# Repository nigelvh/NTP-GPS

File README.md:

# NTP-GPS
Custom GPS Hardware for use with NTP Stratum 1 servers, along with system configuration documentation.

## Hardware
The hardware designs for my specific device. There are many GPS options for building a Stratum 1 NTP server. This is just one take on it.

## Firmware
The firmware code and binaries for the device described in the Hardware section. Built in the Arduino IDE to be maximally approachable.

## Software
Configuration guides for setting up NTPd, NTPsec, or Chrony on Ubuntu, Debian, Alma, or Rocky to acquire the PPS signals provided by the GPS and use them to discipline the local clock and act as a Stratum 1 server.

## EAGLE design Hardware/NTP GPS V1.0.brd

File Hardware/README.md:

# NTP GPS Hardware
This is a custom piece of hardware for use with stratum 1 NTP servers to provide a simple and flexible way of getting timing data into the NTP daemon of choice.

This is not a wholly unique device, there are other devices that perform similar functions or some subset thereof. It is certainly not the only way to accomplish the task. It was designed as a means to address the most common shortfalls I have seen and for the enjoyment of making it.

This device uses a good quality GPS receiver with precise Pulse Per Second (PPS) output, and exposes both the NMEA data, as well as the PPS signal on the DCD serial line over both USB (less precise timing) as well as RS232 (more precise timing) simultaneously. This is done to provide maximum flexibility to the user's use case. If a hardware serial port is available, use that as it will provide more precise timing. If only USB is available, that is also functional.

Many inexpensive off the shelf GPS receivers do not expose the PPS signals properly on the DCD serial line making precise timing difficult to capture, or expensive time servers are available which are double to many times the cost of this device. This device was designed to fit the middle ground of a quality time source for a use case where an existing server is available, and can be configured per the instructions in the Software folder of this repository.

The schematic and board files have been created in Eagle, though I cannot guarantee how they will load without all the the associated libraries. There are additionally exported images of the schematic and board designs available for reference without using the Eagle software package.

A parts text file has been included to cover some of the more important, or more specific parts for the design. It is not all inclusive (I didn't include the passives for example), but it covers the main components, as well as some useful accessories (cables, antenna, etc).

## Design Choices
### ESP32
The ESP32 was chosen as the microcontroller for this project as it is able to handle three simultaneous hardware UARTs, is reasonably inexpensive, and is easily programmed with the Arduino IDE. In some measures it is overkill for this application, but being inexpensive and easily programmable make it more approachable to more people.

### uBlox MAX-M8 GPS
The uBlox MAX-M8 GPS device was chosen for being a quality GPS chipset, that I am familiar with, and has good timing parameters. The MAX series is not the specifically timing oriented line, however it is more than accurate enough for NTP requirements. It is able to track multiple constellations and has good RF sensitivity. I have fitted it with the associated power circuitry to supply an active GPS antenna which is essential for longer runs of cable, which is likely to be required to span between a rooftop antenna placement and a server located inside a building/datacenter.

### FTDI UART and ST232 Serial Driver
There are microcontroller choices available that could do USB natively, as well as there are other RS232 driver chipsets that may be cheaper. These were chosen for being commonly available, widely used and proven, as well as having the required inputs/outputs to handle the PPS signal over the DCD line, which not all devices support.

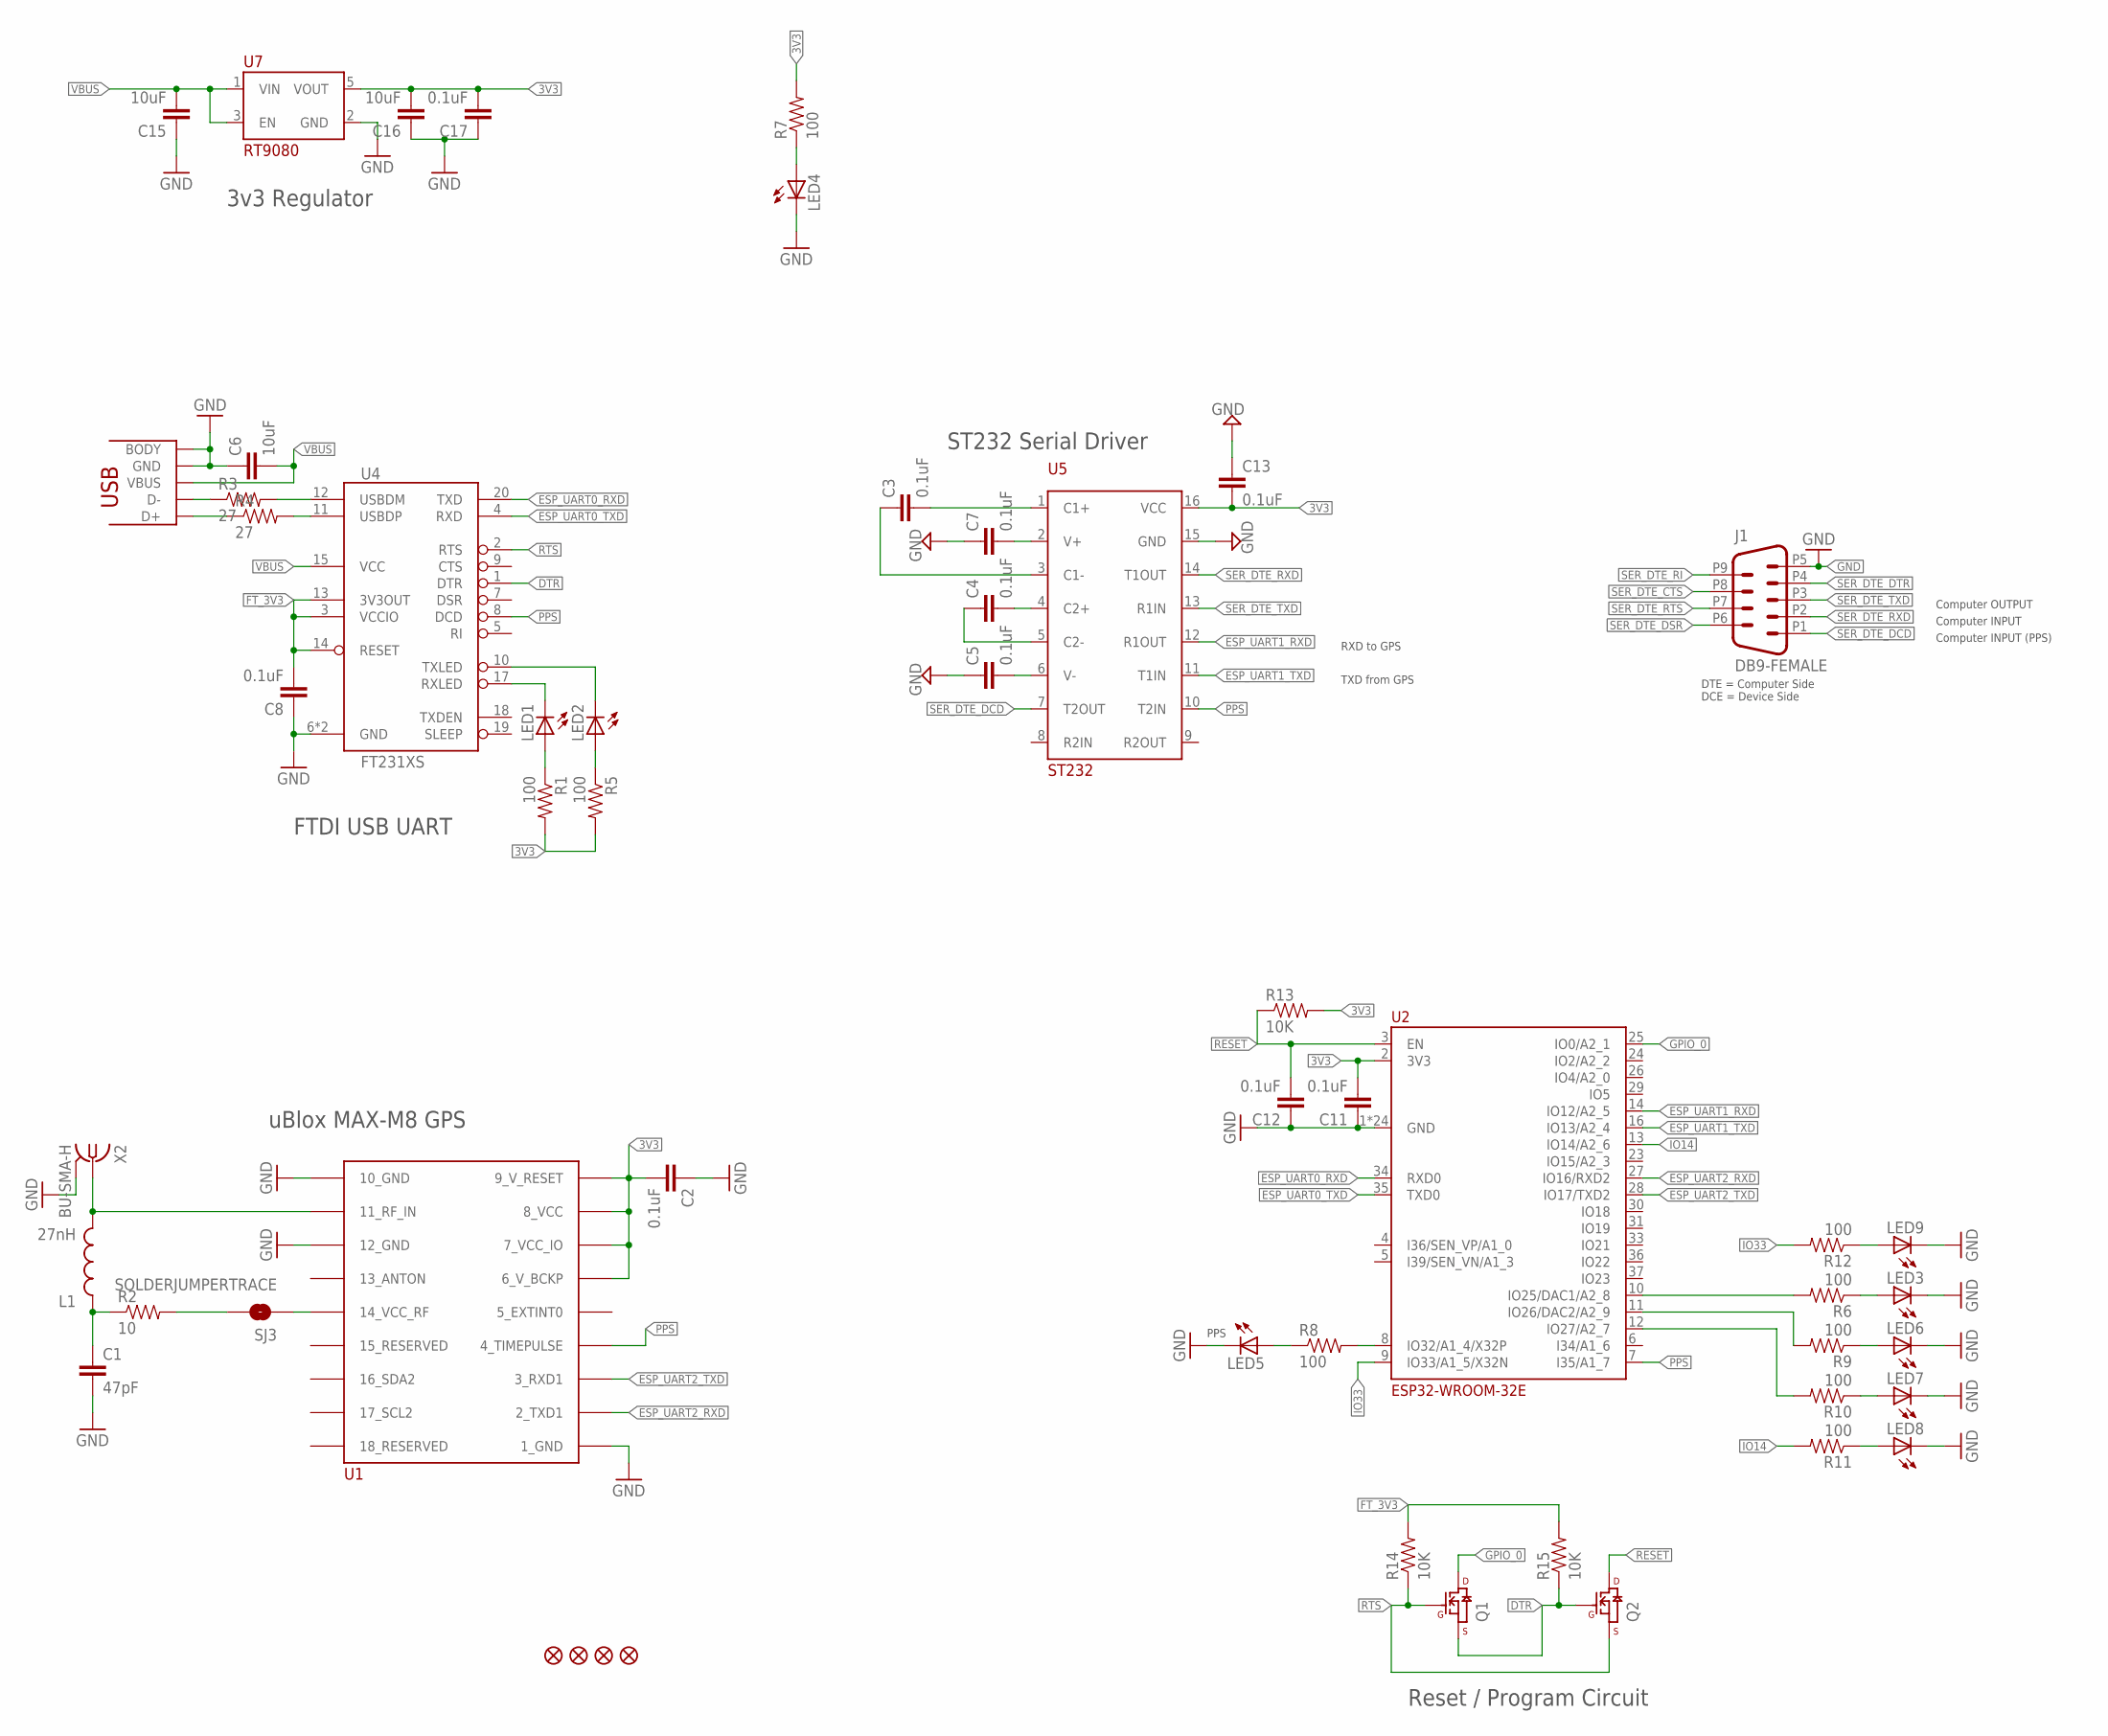
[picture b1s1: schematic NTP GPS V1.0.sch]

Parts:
C1: 47pF; 0603-CAP
C2, C3, C4, C5, C7, C8, C11, C12, C13, C17: 0.1uF; 0603-CAP
C6, C15, C16: 10uF; 1206
FID1, FID2, FID3, FID4: FIDUCIAL
J1: DB9-FEMALE; AMP_DELTAD_D09S13B4GV00LF
L1: 27nH; 0603
LED1, LED2, LED3, LED4, LED5, LED6, LED7, LED8, LED9: LED; LED_QBL7XX80D-MP4A
Q1, Q2: MOSFET_N_CHANNELSI1308; SC-70-3
R1, R5, R6, R7, R8, R9, R10, R11, R12: 100; 0603-RES
R2: 10; 0603-RES
R3, R4: 27; 0603-RES
R13, R14, R15: 10K; 0603-RES
SJ3: SOLDERJUMPERTRACE; SJ_2S-TRACE
U1: UBLOX_MAX
U2: ESP32-WROOM-32E
U4: FT231XS; SSOP-20
U5: ST232; SSOP-16
U7: RT9080; SOT-23-5
U$1: USB-MICROB; USB-MICROB-10118192
X2: BU-SMA-H

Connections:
3V3: C2.2, C11.2, C13.2, C16.2, C17.2, R1.2, R5.2, R7.2, R13.2, U1.6_V_BCKP, U1.7_VCC_IO, U1.8_VCC, U1.9_V_RESET, U2.2 (3V3), U5.16 (VCC), U7.5 (VOUT)
DTR: Q1.P$2 (S), Q2.P$1 (G), R15.1, U4.1 (DTR)
ESP_UART0_RXD: U2.34 (RXD0), U4.20 (TXD)
ESP_UART0_TXD: U2.35 (TXD0), U4.4 (RXD)
ESP_UART1_RXD: U2.14 (IO12/A2_5), U5.12 (R1OUT)
ESP_UART1_TXD: U2.16 (IO13/A2_4), U5.11 (T1IN)
ESP_UART2_RXD: U1.2_TXD1, U2.27 (IO16/RXD2)
ESP_UART2_TXD: U1.3_RXD1, U2.28 (IO17/TXD2)
FT_3V3: C8.2, R14.2, R15.2, U4.3 (VCCIO), U4.13 (3V3OUT), U4.14 (RESET)
GND: C1.2, C2.1, C5.1, C6.1, C7.1, C8.1, C11.1, C12.1, C13.1, C15.1, C16.1, C17.1, J1.P5 (5), LED3.C, LED4.C, LED5.C, LED6.C, LED7.C, LED8.C, LED9.C, U1.1_GND, U1.10_GND, U1.12_GND, U2.1 (GND), U2.15 (GND), U2.38 (GND), U2.P$1 (GND), U2.P$2 (GND), U2.P$3 (GND), U2.P$4 (GND), U2.P$5 (GND), U2.P$6 (GND), U2.P$7 (GND), U2.P$8 (GND), U2.P$9 (GND), U2.P$10 (GND), U2.P$11 (GND), U2.P$12 (GND), U2.PAD@1 (GND), U2.PAD@2 (GND), U2.PAD@3 (GND), U2.PAD@4 (GND), U2.PAD@5 (GND), U2.PAD@6 (GND), U2.PAD@7 (GND), U2.PAD@8 (GND), U2.PAD@9 (GND), U4.6 (GND), U4.16 (GND), U5.15 (GND), U7.2 (GND), U$1.5 (GND), U$1.BODY@1 (BODY), U$1.BODY@2 (BODY), U$1.BODY@3 (BODY), U$1.BODY@4 (BODY), U$1.BODY@5 (BODY), U$1.BODY@6 (BODY), X2.2, X2.3 (2), X2.4 (2), X2.5 (2)
GPIO_0: Q1.P$3 (D), U2.25 (IO0/A2_1)
IO14: R11.2, U2.13 (IO14/A2_6)
IO33: R12.2, U2.9 (IO33/A1_5/X32N)
unnamed: L1.2, U1.11_RF_IN, X2.1
unnamed: R8.2, U2.8 (IO32/A1_4/X32P)
unnamed: SJ3.1, U1.14_VCC_RF
unnamed: C1.1, L1.1, R2.1
unnamed: C7.2, U5.2 (V+)
unnamed: C5.2, U5.6 (V-)
unnamed: R3.1, U$1.2 (D-)
unnamed: R4.1, U$1.3 (D+)
unnamed: LED2.A, R5.1
unnamed: C3.2, U5.1 (C1+)
unnamed: LED3.A, R6.1
unnamed: C4.2, U5.4 (C2+)
unnamed: LED1.C, U4.17 (RXLED)
unnamed: C3.1, U5.3 (C1-)
unnamed: C4.1, U5.5 (C2-)
unnamed: LED2.C, U4.10 (TXLED)
unnamed: R4.2, U4.11 (USBDP)
unnamed: R3.2, U4.12 (USBDM)
unnamed: R2.2, SJ3.2
unnamed: LED4.A, R7.1
unnamed: LED5.A, R8.1
unnamed: LED1.A, R1.1
unnamed: LED6.A, R9.1
unnamed: LED7.A, R10.1
unnamed: LED8.A, R11.1
unnamed: LED9.A, R12.1
unnamed: R6.2, U2.10 (IO25/DAC1/A2_8)
unnamed: R9.2, U2.11 (IO26/DAC2/A2_9)
unnamed: R10.2, U2.12 (IO27/A2_7)
PPS: U1.4_TIMEPULSE, U2.7 (I35/A1_7), U4.8 (DCD), U5.10 (T2IN)
RESET: C12.2, Q2.P$3 (D), R13.1, U2.3 (EN)
RTS: Q1.P$1 (G), Q2.P$2 (S), R14.1, U4.2 (RTS)
SER_DTE_CTS: J1.P8 (8)
SER_DTE_DCD: J1.P1 (1), U5.7 (T2OUT)
SER_DTE_DSR: J1.P6 (6)
SER_DTE_DTR: J1.P4 (4)
SER_DTE_RI: J1.P9 (9)
SER_DTE_RTS: J1.P7 (7)
SER_DTE_RXD: J1.P2 (2), U5.14 (T1OUT)
SER_DTE_TXD: J1.P3 (3), U5.13 (R1IN)
VBUS: C6.2, C15.2, U4.15 (VCC), U7.1 (VIN), U7.3 (EN), U$1.1 (VBUS)

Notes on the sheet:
FTDI USB UART
DTE = Computer Side DCE = Device Side
Computer INPUT
Computer OUTPUT
Computer INPUT (PPS)
TXD from GPS
RXD to GPS
3v3 Regulator
Reset / Program Circuit
PPS
ST232 Serial Driver
uBlox MAX-M8 GPS

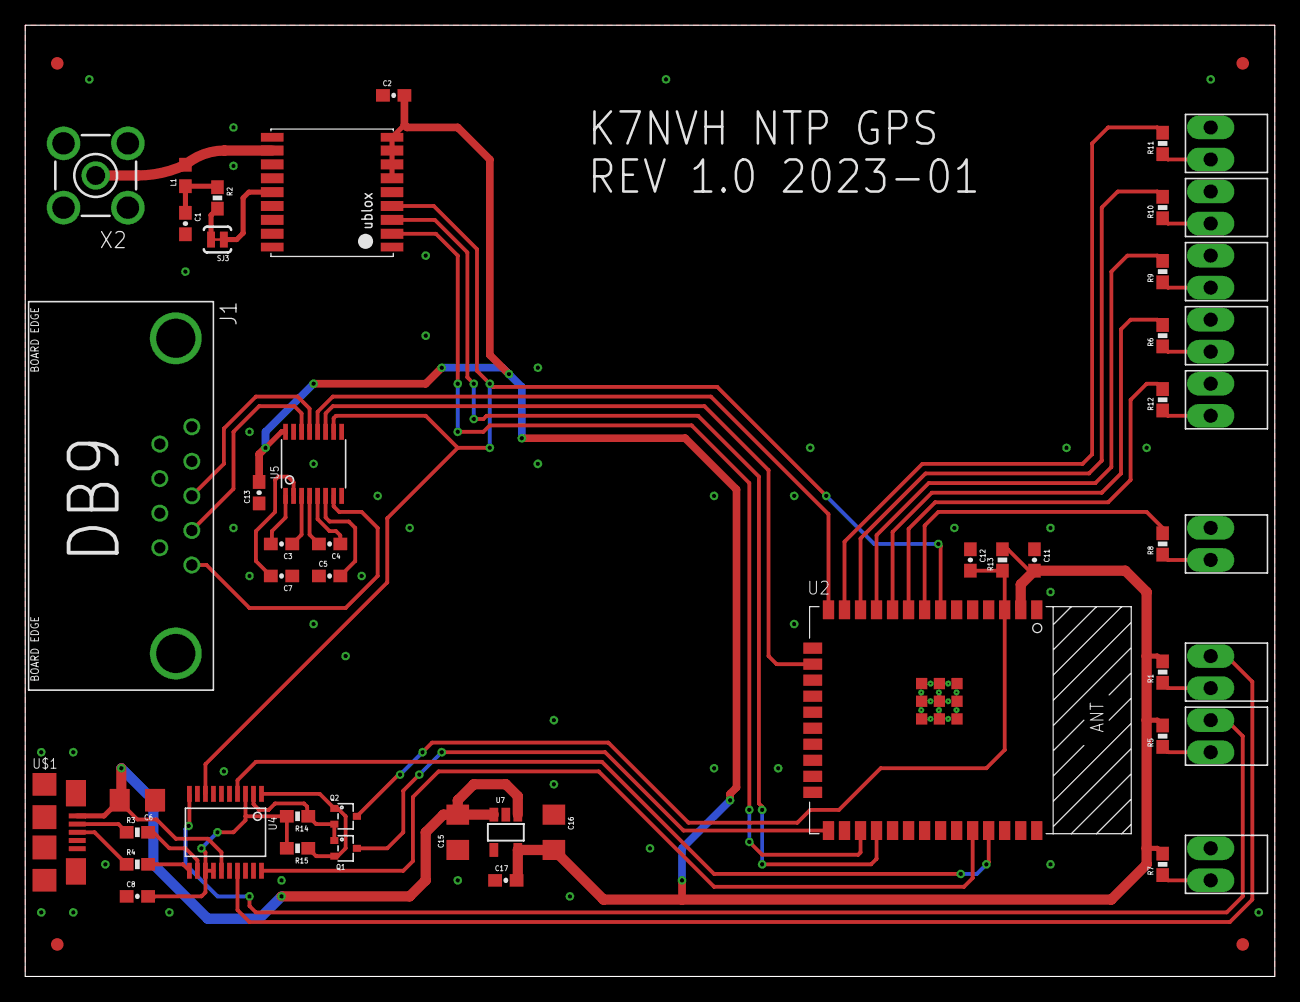
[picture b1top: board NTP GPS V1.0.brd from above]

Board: 2 copper layers, 99.1 x 75.4 mm, 54 parts (0 on the bottom side), 49 nets.

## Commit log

2023-01-14 Initial firmware commit.
2023-01-14 Add initial gpsd and ntpd configs.
2023-01-14 Initial software configuration instructions.
2023-01-14 Tweak screenshot image size.
2023-01-15 Add the start of a TOC.
2023-01-15 Add chrony instructions.
2023-01-16 Remove the stats entries from the ntpd example conf. Not used in the example.
2023-01-16 Add NTPsec configuration and instructions.
2023-01-16 Tweak order of operations.
2023-01-16 Add debian to the instructions.
2023-01-16 Tweak TOC name.
2023-01-19 Initial Alma config instructions.
2023-01-19 Add AlmaLinux to the TOC.
2023-01-19 Fix section link.
2023-01-20 Tweak chrony config to allow for coarse time being set from GPS when no internet peers are available.
2023-01-20 Rocky works with same Alma instructions.
2023-01-20 Tweak TOC
2023-01-20 Add a bit more context.
2023-01-20 Move firmware binaries into a dedicated folder.
2023-01-20 Add designs, images, and readme to the Hardware directory.
2023-01-20 Added some hardware choices info.
2023-01-20 Updated main repo README.

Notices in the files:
parts and their libraries:
SparkFun: Licensing: CC v3.0 Share-Alike You are welcome to use this library for commercial purposes.
